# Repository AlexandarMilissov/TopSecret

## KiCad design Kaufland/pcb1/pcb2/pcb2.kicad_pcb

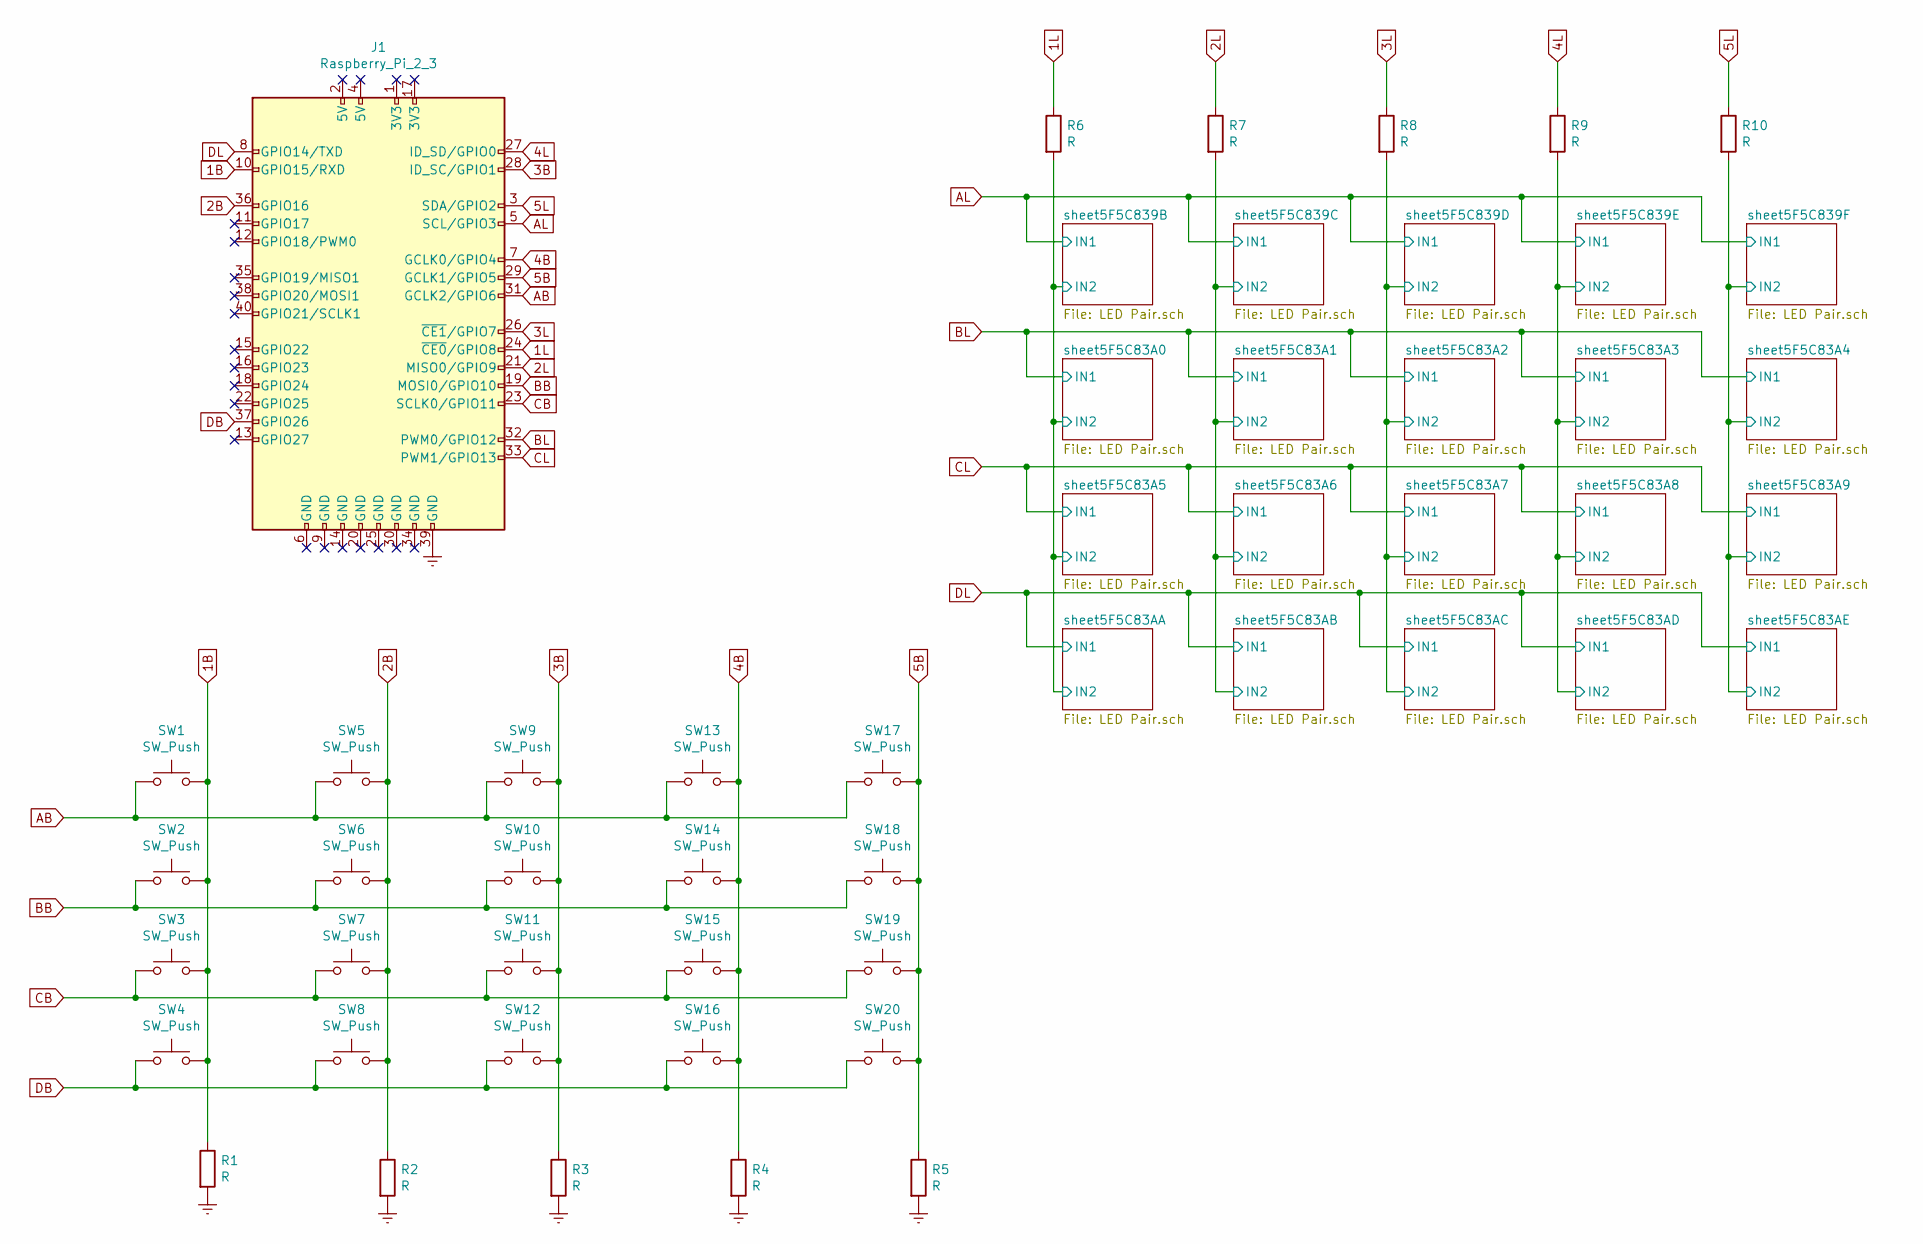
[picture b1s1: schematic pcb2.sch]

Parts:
J1: Raspberry_Pi_2_3; MODULE_RASPBERRY_PI_3_MODEL_B+
R1, R2, R3, R4, R5, R6, R7, R8, R9, R10: R; R_Axial_DIN0204_L3.6mm_D1.6mm_P5.08mm_Horizontal
SW1, SW2, SW3, SW4, SW5, SW6, SW7, SW8, SW9, SW10, SW11, SW12, SW13, SW14, SW15, SW16, SW17, SW18, SW19, SW20: SW_Push; PinSocket_2x01_P2.54mm_Vertical

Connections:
1B: J1.10 (GPIO15/RXD), R1.1, SW1.2, SW2.2, SW3.2, SW4.2
1L: J1.24 (~CE0~/GPIO8), R6.1
2B: J1.36 (GPIO16), R2.1, SW5.2, SW6.2, SW7.2, SW8.2
2L: J1.21 (MISO0/GPIO9), R7.1
3B: J1.28 (ID_SC/GPIO1), R3.1, SW9.2, SW10.2, SW11.2, SW12.2
3L: J1.26 (~CE1~/GPIO7), R8.1
4B: J1.7 (GCLK0/GPIO4), R4.1, SW13.2, SW14.2, SW15.2, SW16.2
4L: J1.27 (ID_SD/GPIO0), R9.1
5B: J1.29 (GCLK1/GPIO5), R5.1, SW17.2, SW18.2, SW19.2, SW20.2
5L: J1.3 (SDA/GPIO2), R10.1
/sheet5F5C839B/IN2: R6.2; also elsewhere on the board
/sheet5F5C839C/IN2: R7.2; also elsewhere on the board
/sheet5F5C839D/IN2: R8.2; also elsewhere on the board
/sheet5F5C839E/IN2: R9.2; also elsewhere on the board
/sheet5F5C839F/IN2: R10.2; also elsewhere on the board
AB: J1.31 (GCLK2/GPIO6), SW1.1, SW5.1, SW9.1, SW13.1, SW17.1
AL: J1.5 (SCL/GPIO3); also elsewhere on the board
BB: J1.19 (MOSI0/GPIO10), SW2.1, SW6.1, SW10.1, SW14.1, SW18.1
BL: J1.32 (PWM0/GPIO12); also elsewhere on the board
CB: J1.23 (SCLK0/GPIO11), SW3.1, SW7.1, SW11.1, SW15.1, SW19.1
CL: J1.33 (PWM1/GPIO13); also elsewhere on the board
DB: J1.37 (GPIO26), SW4.1, SW8.1, SW12.1, SW16.1, SW20.1
DL: J1.8 (GPIO14/TXD); also elsewhere on the board
Earth: J1.39 (GND), R1.2, R2.2, R3.2, R4.2, R5.2

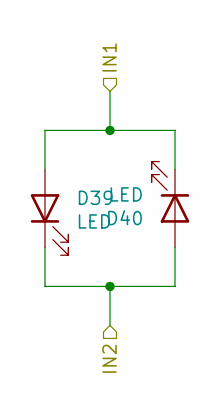
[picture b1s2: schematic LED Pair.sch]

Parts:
D1, D2: LED; PinSocket_2x01_P2.54mm_Horizontal

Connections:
/sheet5F5C839B/IN2: D1.1 (K), D2.2 (A); also elsewhere on the board
AL: D1.2 (A), D2.1 (K); also elsewhere on the board

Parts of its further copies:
D3, D4, D5, D6, D7, D8, D9, D10, D11, D12, D13, D14, D15, D16, D17, D18, D19, D20, D21, D22, D23, D24, D25, D26, D27, D28, D29, D30, D31, D32, D33, D34, D35, D36, D37, D38, D39, D40: LED; PinSocket_2x01_P2.54mm_Horizontal

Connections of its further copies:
/sheet5F5C839B/IN2: D11.1 (K), D12.2 (A), D21.1 (K), D22.2 (A), D31.1 (K), D32.2 (A); also elsewhere on the board
/sheet5F5C839C/IN2: D3.1 (K), D4.2 (A), D13.1 (K), D14.2 (A), D23.1 (K), D24.2 (A), D33.1 (K), D34.2 (A); also elsewhere on the board
/sheet5F5C839D/IN2: D5.1 (K), D6.2 (A), D15.1 (K), D16.2 (A), D25.1 (K), D26.2 (A), D35.1 (K), D36.2 (A); also elsewhere on the board
/sheet5F5C839E/IN2: D7.1 (K), D8.2 (A), D17.1 (K), D18.2 (A), D27.1 (K), D28.2 (A), D37.1 (K), D38.2 (A); also elsewhere on the board
/sheet5F5C839F/IN2: D9.1 (K), D10.2 (A), D19.1 (K), D20.2 (A), D29.1 (K), D30.2 (A), D39.1 (K), D40.2 (A); also elsewhere on the board
AL: D3.2 (A), D4.1 (K), D5.2 (A), D6.1 (K), D7.2 (A), D8.1 (K), D9.2 (A), D10.1 (K); also elsewhere on the board
BL: D11.2 (A), D12.1 (K), D13.2 (A), D14.1 (K), D15.2 (A), D16.1 (K), D17.2 (A), D18.1 (K), D19.2 (A), D20.1 (K); also elsewhere on the board
CL: D21.2 (A), D22.1 (K), D23.2 (A), D24.1 (K), D25.2 (A), D26.1 (K), D27.2 (A), D28.1 (K), D29.2 (A), D30.1 (K); also elsewhere on the board
DL: D31.2 (A), D32.1 (K), D33.2 (A), D34.1 (K), D35.2 (A), D36.1 (K), D37.2 (A), D38.1 (K), D39.2 (A), D40.1 (K); also elsewhere on the board

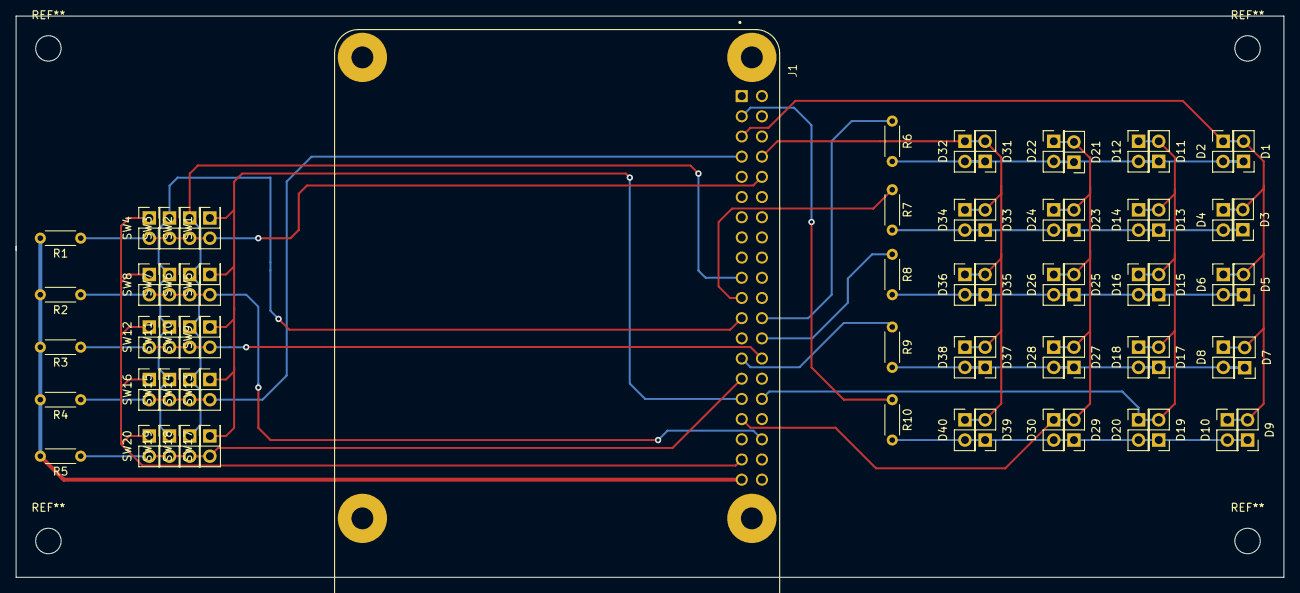
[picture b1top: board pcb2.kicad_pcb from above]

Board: 2 copper layers, 159.5 x 70.6 mm, 71 parts (0 on the bottom side), 24 nets.

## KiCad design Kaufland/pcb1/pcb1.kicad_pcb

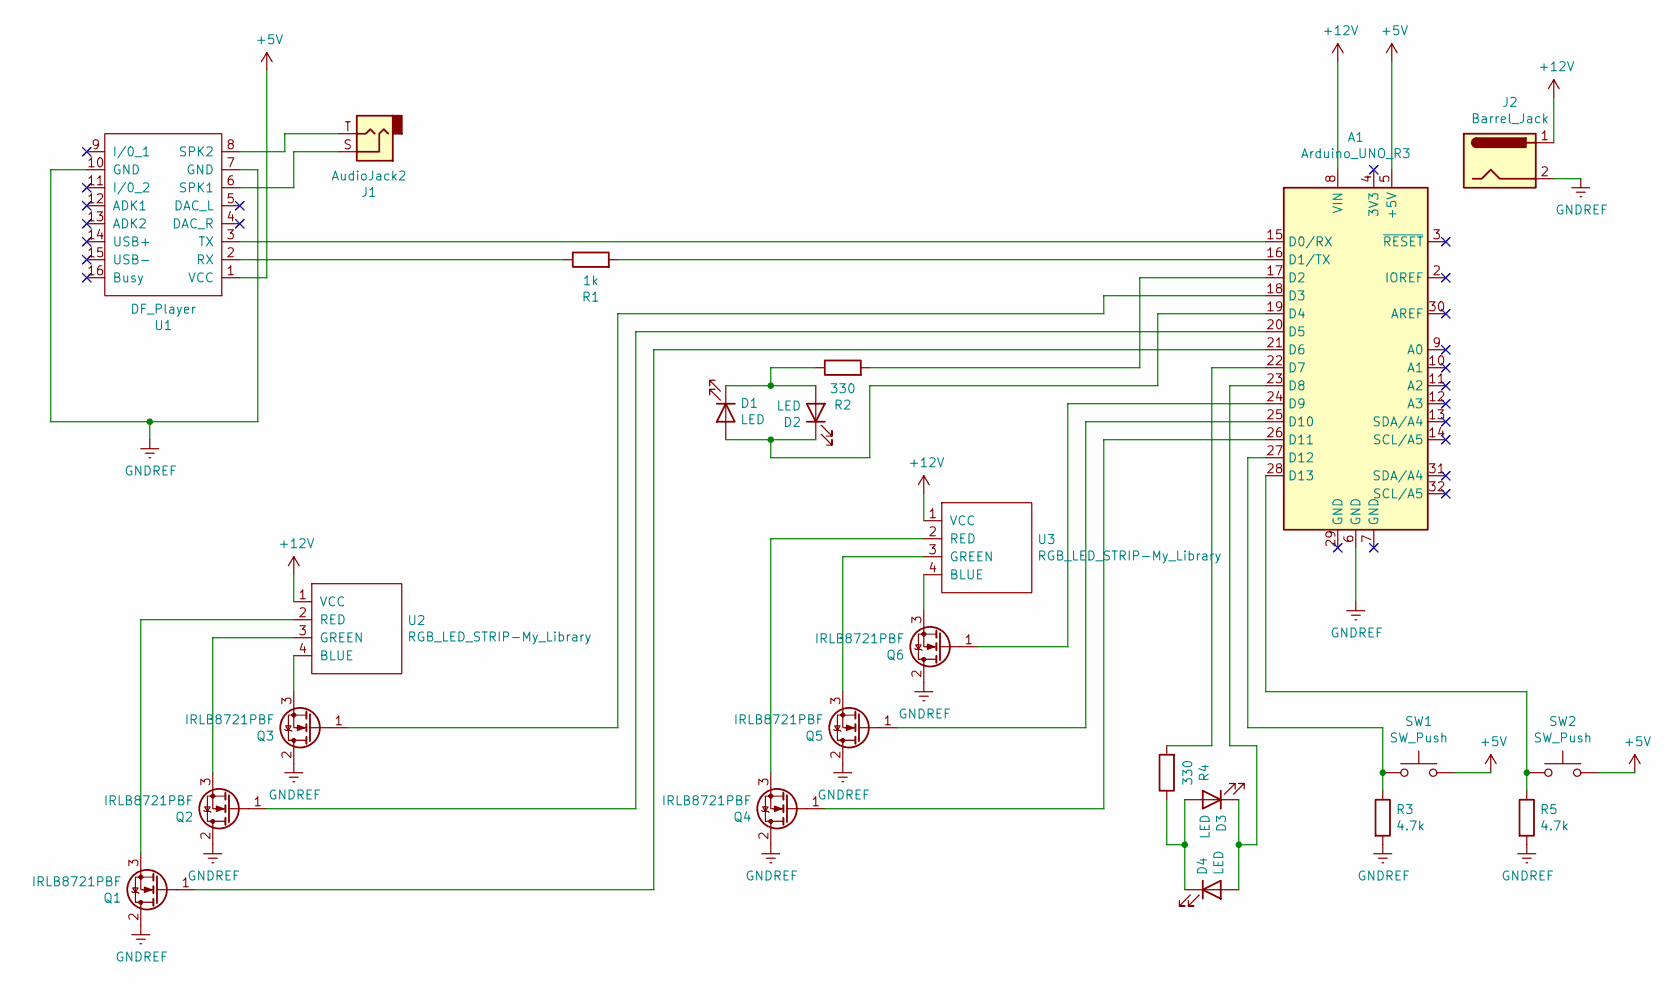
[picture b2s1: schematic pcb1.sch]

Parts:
A1: Arduino_UNO_R3
D1, D2, D3, D4: LED; FanPinHeader_1x03_P2.54mm_Vertical
J1: AudioJack2; Jack_3.5mm_PJ320E_Horizontal
J2: Barrel_Jack; BarrelJack_CUI_PJ-063AH_Horizontal
Q1, Q2, Q3, Q4, Q5, Q6: IRLB8721PBF; TO-220-3_Vertical
R1: 1k; R_Axial_DIN0204_L3.6mm_D1.6mm_P7.62mm_Horizontal
R2, R4: 330; R_Axial_DIN0204_L3.6mm_D1.6mm_P7.62mm_Horizontal
R3, R5: 4.7k; R_Axial_DIN0204_L3.6mm_D1.6mm_P7.62mm_Horizontal
SW1, SW2: SW_Push; FanPinHeader_1x03_P2.54mm_Vertical
U1: DF_Player; DFPlayerMini
U2, U3: RGB_LED_STRIP-My_Library; JST_EH_S4B-EH_1x04_P2.50mm_Horizontal

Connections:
+5V: A1.5 (+5V), SW1.2, SW2.2, U1.1 (VCC)
+12V: A1.8 (VIN), J2.1, U2.1 (VCC), U3.1 (VCC)
GNDREF: A1.6 (GND), J2.2, Q1.2 (D), Q2.2 (D), Q3.2 (D), Q4.2 (D), Q5.2 (D), Q6.2 (D), R3.2, R5.2, U1.7 (GND), U1.10 (GND)
unnamed: A1.15 (D0/RX), U1.3 (TX)
unnamed: A1.16 (D1/TX), R1.2
unnamed: A1.17 (D2), R2.2
unnamed: A1.18 (D3), Q3.1 (G)
unnamed: A1.19 (D4), D1.2 (A), D2.1 (K)
unnamed: A1.20 (D5), Q2.1 (G)
unnamed: A1.21 (D6), Q1.1 (G)
unnamed: A1.22 (D7), R4.2
unnamed: A1.23 (D8), D3.1 (K), D4.2 (A)
unnamed: A1.24 (D9), Q6.1 (G)
unnamed: A1.25 (D10), Q5.1 (G)
unnamed: A1.26 (D11), Q4.1 (G)
unnamed: A1.27 (D12), R3.1, SW1.1
unnamed: A1.28 (D13), R5.1, SW2.1
unnamed: D1.1 (K), D2.2 (A), R2.1
unnamed: D3.2 (A), D4.1 (K), R4.1
unnamed: J1.S, U1.6 (SPK1)
unnamed: J1.T, U1.8 (SPK2)
unnamed: Q1.3 (S), U2.2 (RED)
unnamed: Q2.3 (S), U2.3 (GREEN)
unnamed: Q3.3 (S), U2.4 (BLUE)
unnamed: Q4.3 (S), U3.2 (RED)
unnamed: Q5.3 (S), U3.3 (GREEN)
unnamed: Q6.3 (S), U3.4 (BLUE)
unnamed: R1.1, U1.2 (RX)

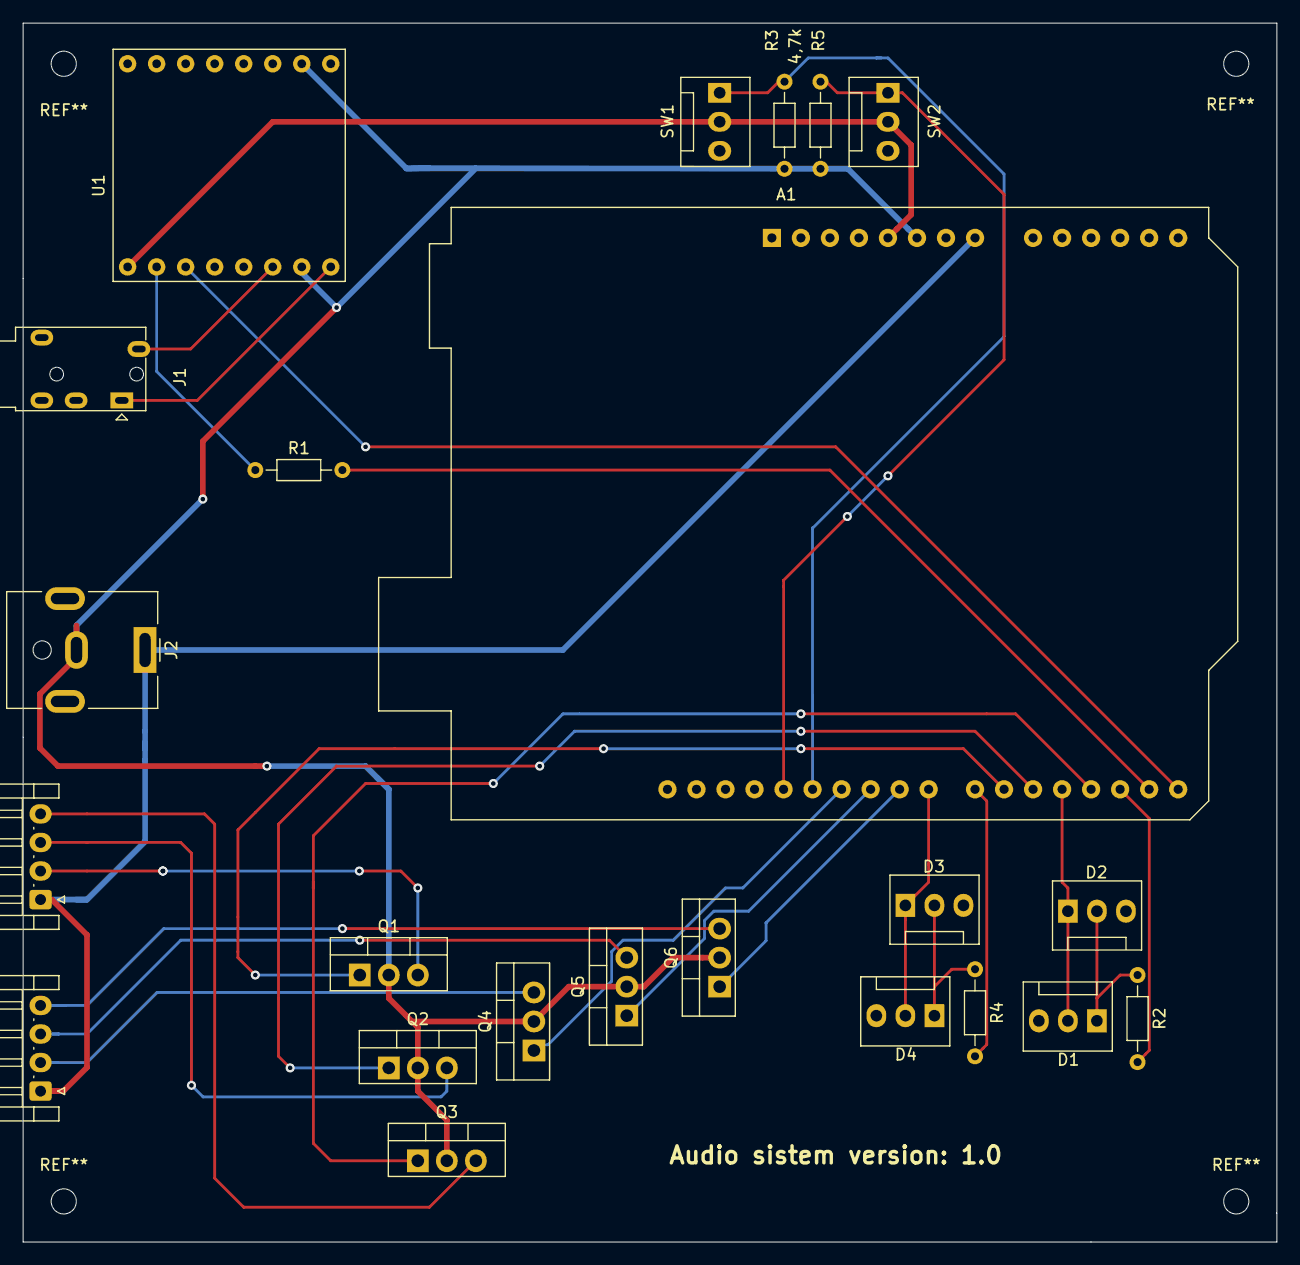
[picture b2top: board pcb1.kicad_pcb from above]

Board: 2 copper layers, 109.7 x 106.7 mm, 23 parts (0 on the bottom side), 28 nets.

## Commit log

2020-08-10 First pcb model (to be fixed)
2020-08-11 Flipped pcb (to be checked; routed)
2020-08-11 small changes to the pcb
2020-08-12 added additional strip 2 more leds and a button to pcb
2020-08-12 finished pcb v1.0
2020-08-17 finished 3d model v1
2020-08-17 added exlpode and
2020-08-17 Changed pins for LED strips
2020-08-18 bugfixing pcb
2020-08-19 box v2
2020-09-08 pcb2 routed
2020-09-08 update box v4
2020-09-09 updatred dimentions
